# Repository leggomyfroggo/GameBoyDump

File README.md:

# GameBoyDump
Random stuff I've made for Game Boy Projects.

Licensed under [CC-BY-SA](https://creativecommons.org/licenses/by-sa/4.0/)

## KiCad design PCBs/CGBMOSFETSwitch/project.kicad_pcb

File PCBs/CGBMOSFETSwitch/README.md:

# Overview

This is a replacement power switch circuit for the Game Boy Color that utilizes MOSFETs to switch system power, rather than shunting it directly through the physical switch. In theory, this should ensure proper functionality even when the switch is dirty.

# Disclaimer
I have installed this in one GBC, and it continues to work after ~3 years, but I can't make specific claims about longevity.

# BOM
| Designator | Description | Footprint | Part # |
| ---------- | ----------- | --------- | ------ |
| R1 | 10K | 0603 | - |
| Q2, Q3 | P-FET | SOT-23 | DMP6350SQ-7 |
| Q1 | N-FET | SOT-23 | SI2312BDS-T1-BE3 |
| SW1 | SP3T switch | - | MSKT-13C01 |

# License
<a href="github.com/leggomyfroggo/GameBoyDump/PCBs/CGBMOSFETSwitch">CGB MOSFET Switch</a> © 2022 by <a href="github.com/LeggoMyFroggo">Chris Hackmann</a> is licensed under <a href="https://creativecommons.org/licenses/by-nc-sa/4.0/">CC BY-NC-SA 4.0</a>

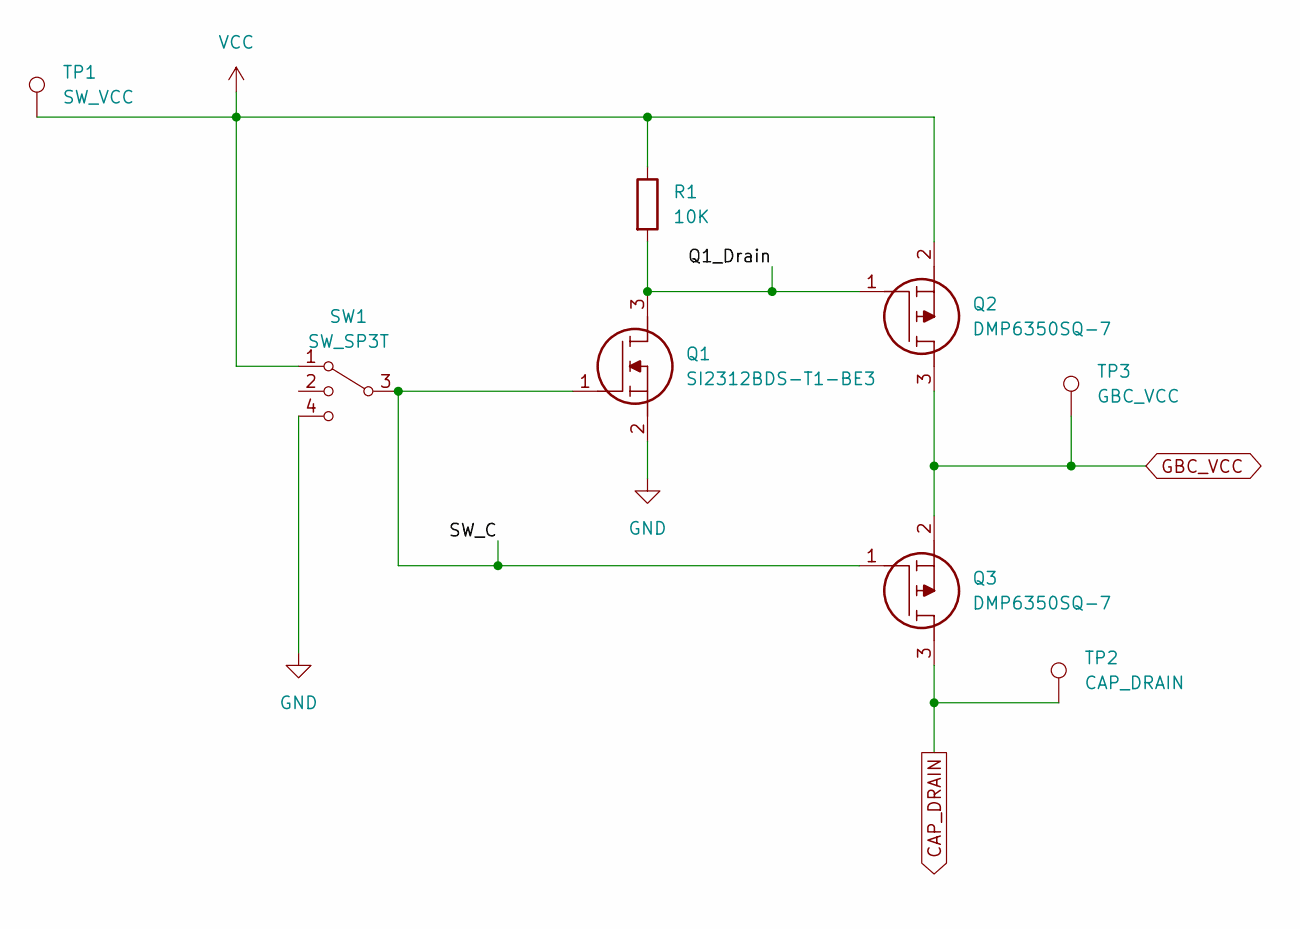
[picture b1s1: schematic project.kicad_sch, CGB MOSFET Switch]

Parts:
Q1: SI2312BDS-T1-BE3; SOT95P237X112-3N; Mouser Part Number 78-SI2312BDS-T1-BE3
Q2, Q3: DMP6350SQ-7; SOT96P240X110-3N; Mouser Part Number 621-DMP6350SQ-7
R1: 10K; R_0603_1608Metric
SW1: SW_SP3T; MSKT-13C01
TP1: SW_VCC; TestPoint_Pad_D1.0mm
TP2: CAP_DRAIN; TestPoint_Pad_D1.0mm
TP3: GBC_VCC; TestPoint_Pad_D1.0mm

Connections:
/Q1_Drain: Q1.3, Q2.1, R1.2
/SW_C: Q1.1, Q3.1, SW1.3
CAP_DRAIN: Q3.3, TP2.1
GBC_VCC: Q2.3, Q3.2, TP3.1
GND: Q1.2, SW1.4, SW1.5
VCC: Q2.2, R1.1, SW1.1, TP1.1

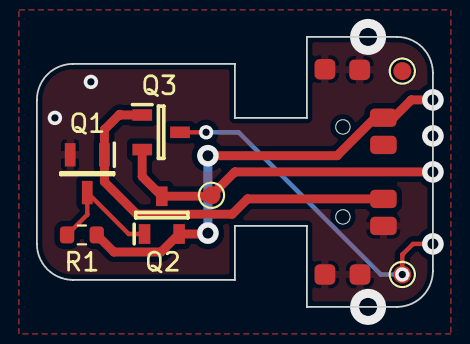
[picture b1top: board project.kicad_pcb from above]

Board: 2 copper layers, 22.0 x 15.0 mm, 8 parts (0 on the bottom side), 6 nets.

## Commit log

2024-05-19 Update README.md
    Add license
2024-05-19 Add model for AGS cart slot
2024-05-19 Adding images and readme
2025-05-21 Add mosfet switch for GBC
